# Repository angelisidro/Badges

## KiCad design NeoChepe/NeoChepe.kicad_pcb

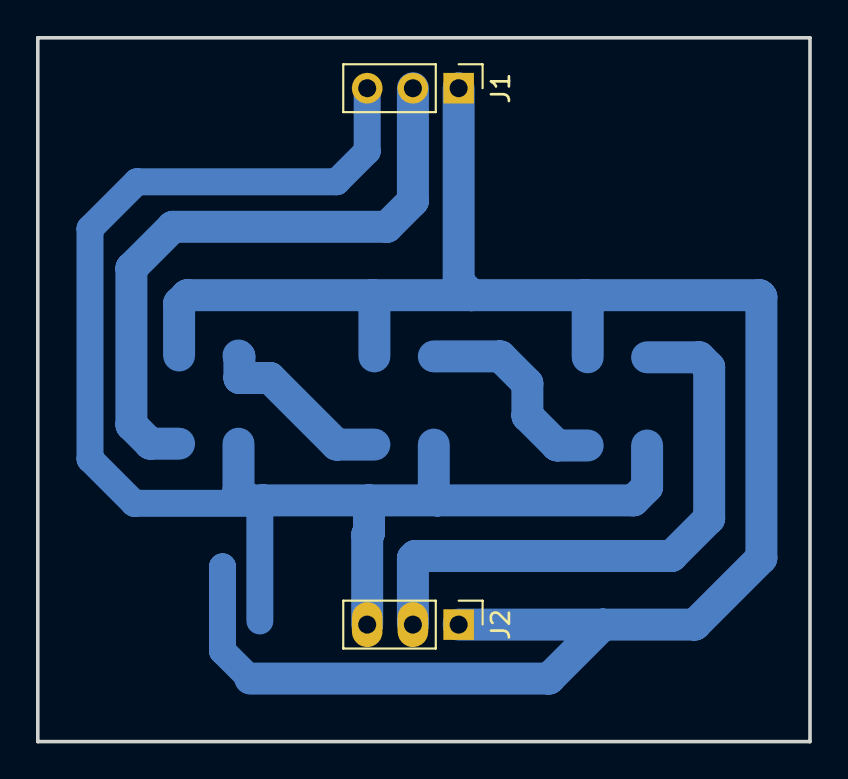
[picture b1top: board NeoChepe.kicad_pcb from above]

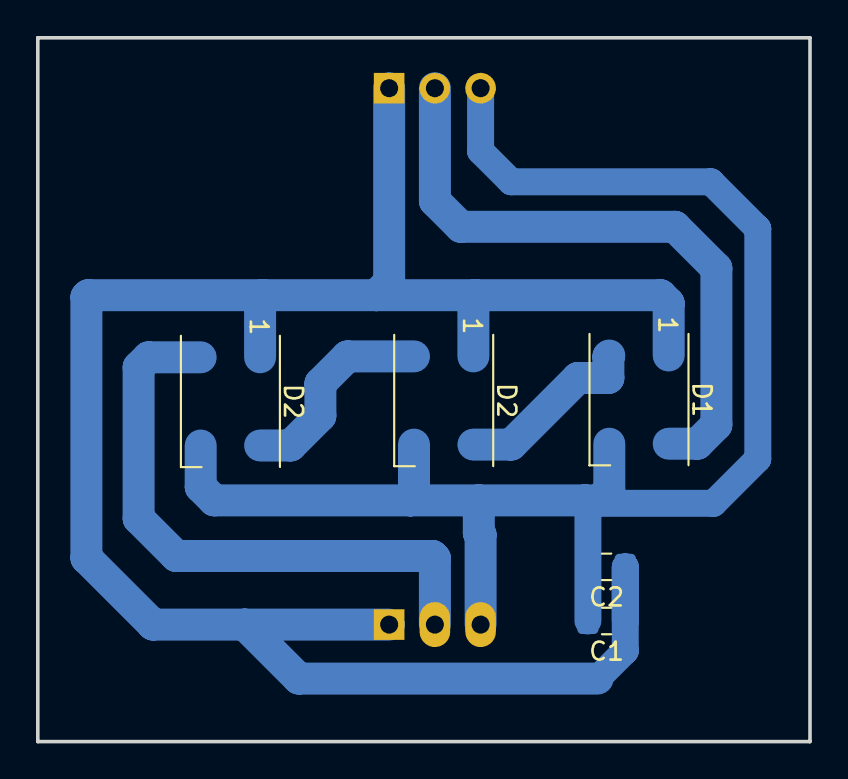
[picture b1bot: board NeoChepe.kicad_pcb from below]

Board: 2 copper layers, 42.9 x 39.1 mm, 7 parts (5 on the bottom side), 5 nets.

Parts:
C1, C2: C; C_0805_2012Metric_Pad1.18x1.45mm_HandSolder
D1, D2, D2#2: WS2812B; LED_WS2812B_PLCC4_5.0x5.0mm_P3.2mm
J1, J2: Conn_01x03_Pin; PinHeader_1x03_P2.54mm_Vertical

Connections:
/neo_out: D2.2 (DOUT), J2.2
/neo_sig: D1.4 (DIN), J1.2
GND: C1.2, C2.2, D1.3 (VSS), D2.3 (VSS), D2#2.3 (VSS), J1.3, J2.3
unnamed: D1.2 (DOUT), D2#2.4 (DIN)
VCC: C1.1, C2.1, D1.1 (VDD), D2.1 (VDD), D2#2.1 (VDD), J1.1, J2.1

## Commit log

2024-05-14 Badge Balam
2024-07-16 cambios
2024-07-19 BADGE TETTSA
2024-07-22 avances
2025-06-25 Avances FIT
2025-06-25 Diseño finalizado
